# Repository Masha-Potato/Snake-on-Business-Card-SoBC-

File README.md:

sobc.kicad_pcb, sobc.kicad_pro, and sobc.kicad_sch are the relevant files to view and edit PCB, the rest are manufacturing files for JLCPCB.

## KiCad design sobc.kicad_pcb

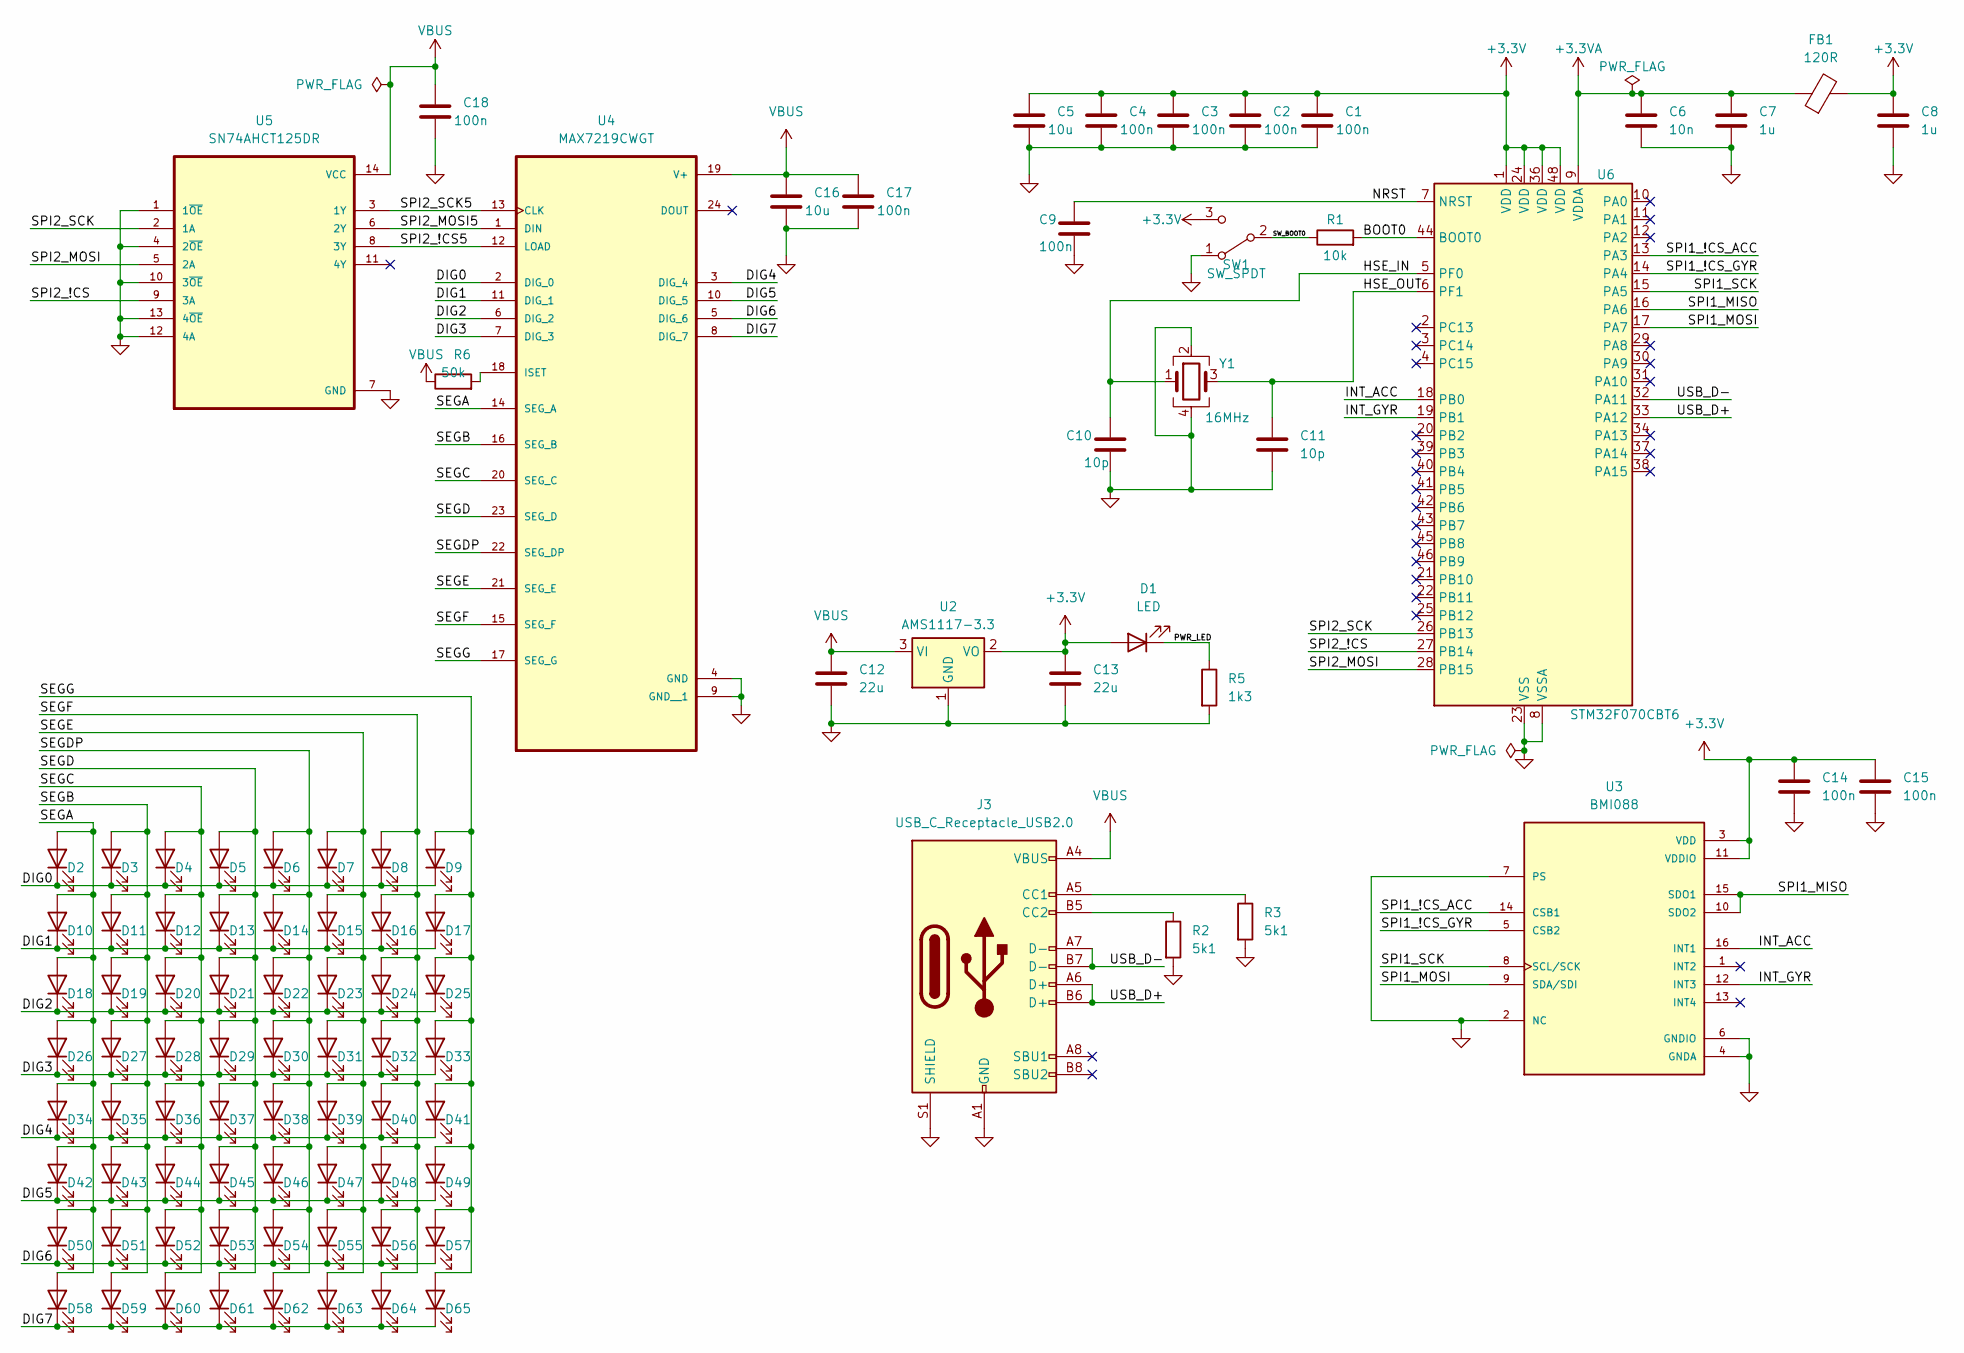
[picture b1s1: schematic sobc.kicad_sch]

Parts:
C1, C2, C3, C4, C9, C14, C15, C17, C18: 100n; C_0402_1005Metric
C5, C16: 10u; C_0603_1608Metric
C6: 10n; C_0402_1005Metric
C7, C8: 1u; C_0402_1005Metric
C10, C11: 10p; C_0402_1005Metric
C12, C13: 22u; C_0805_2012Metric
D1, D2, D3, D4, D5, D6, D7, D8, D9, D10, D11, D12, D13, D14, D15, D16, D17, D18, D19, D20, D21, D22, D23, D24, D25, D26, D27, D28, D29, D30, D31, D32, D33, D34, D35, D36, D37, D38, D39, D40, D41, D42, D43, D44, D45, D46, D47, D48, D49, D50, D51, D52, D53, D54, D55, D56, D57, D58, D59, D60, D61, D62, D63, D64, D65: LED; LED_0603_1608Metric
FB1: 120R; L_0603_1608Metric
J3: USB_C_Receptacle_USB2.0; USB_C_Receptacle_HRO_TYPE-C-31-M-12
R1: 10k; R_0402_1005Metric
R2, R3: 5k1; R_0402_1005Metric
R5: 1k3; R_0402_1005Metric
R6: 50k; R_0402_1005Metric
SW1: SW_SPDT; SW_SPDT_PCM12
U2: AMS1117-3.3; SOT-223-3_TabPin2
U3: BMI088; PQFN50P450X300X100-16N
U4: MAX7219CWGT; SOIC127P1032X265-24N
U5: SN74AHCT125DR; SOIC127P600X175-14N
U6: STM32F070CBT6; LQFP-48_7x7mm_P0.5mm
Y1: 16MHz; Crystal_SMD_3225-4Pin_3.2x2.5mm

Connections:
+3.3V: C1.1, C2.1, C3.1, C4.1, C5.1, C8.1, C13.1, C14.1, C15.1, D1.2 (A), FB1.2, SW1.3 (C), U2.2 (VO), U3.3 (VDD), U3.11 (VDDIO), U6.1 (VDD), U6.24 (VDD), U6.36 (VDD), U6.48 (VDD); also elsewhere on the board
+3.3VA: C6.1, C7.1, FB1.1, U6.9 (VDDA)
/BOOT0: R1.2, U6.44 (BOOT0)
/DIG0: D2.1 (K), D3.1 (K), D4.1 (K), D5.1 (K), D6.1 (K), D7.1 (K), D8.1 (K), D9.1 (K), U4.2 (DIG_0); also elsewhere on the board
/DIG1: D10.1 (K), D11.1 (K), D12.1 (K), D13.1 (K), D14.1 (K), D15.1 (K), D16.1 (K), D17.1 (K), U4.11 (DIG_1); also elsewhere on the board
/DIG2: D18.1 (K), D19.1 (K), D20.1 (K), D21.1 (K), D22.1 (K), D23.1 (K), D24.1 (K), D25.1 (K), U4.6 (DIG_2); also elsewhere on the board
/DIG3: D26.1 (K), D27.1 (K), D28.1 (K), D29.1 (K), D30.1 (K), D31.1 (K), D32.1 (K), D33.1 (K), U4.7 (DIG_3); also elsewhere on the board
/DIG4: D34.1 (K), D35.1 (K), D36.1 (K), D37.1 (K), D38.1 (K), D39.1 (K), D40.1 (K), D41.1 (K), U4.3 (DIG_4); also elsewhere on the board
/DIG5: D42.1 (K), D43.1 (K), D44.1 (K), D45.1 (K), D46.1 (K), D47.1 (K), D48.1 (K), D49.1 (K), U4.10 (DIG_5); also elsewhere on the board
/DIG6: D50.1 (K), D51.1 (K), D52.1 (K), D53.1 (K), D54.1 (K), D55.1 (K), D56.1 (K), D57.1 (K), U4.5 (DIG_6); also elsewhere on the board
/DIG7: D58.1 (K), D59.1 (K), D60.1 (K), D61.1 (K), D62.1 (K), D63.1 (K), D64.1 (K), D65.1 (K), U4.8 (DIG_7); also elsewhere on the board
/HSE_IN: C10.1, U6.5 (PF0), Y1.1
/HSE_OUT: C11.1, U6.6 (PF1), Y1.3
/INT_ACC: U3.16 (INT1), U6.18 (PB0)
/INT_GYR: U3.12 (INT3), U6.19 (PB1)
/NRST: C9.1, U6.7 (NRST)
/PWR_LED: D1.1 (K), R5.1
/SEGA: D2.2 (A), D10.2 (A), D18.2 (A), D26.2 (A), D34.2 (A), D42.2 (A), D50.2 (A), D58.2 (A), U4.14 (SEG_A); also elsewhere on the board
/SEGB: D3.2 (A), D11.2 (A), D19.2 (A), D27.2 (A), D35.2 (A), D43.2 (A), D51.2 (A), D59.2 (A), U4.16 (SEG_B); also elsewhere on the board
/SEGC: D4.2 (A), D12.2 (A), D20.2 (A), D28.2 (A), D36.2 (A), D44.2 (A), D52.2 (A), D60.2 (A), U4.20 (SEG_C); also elsewhere on the board
/SEGD: D5.2 (A), D13.2 (A), D21.2 (A), D29.2 (A), D37.2 (A), D45.2 (A), D53.2 (A), D61.2 (A), U4.23 (SEG_D); also elsewhere on the board
/SEGDP: D6.2 (A), D14.2 (A), D22.2 (A), D30.2 (A), D38.2 (A), D46.2 (A), D54.2 (A), D62.2 (A), U4.22 (SEG_DP); also elsewhere on the board
/SEGE: D7.2 (A), D15.2 (A), D23.2 (A), D31.2 (A), D39.2 (A), D47.2 (A), D55.2 (A), D63.2 (A), U4.21 (SEG_E); also elsewhere on the board
/SEGF: D8.2 (A), D16.2 (A), D24.2 (A), D32.2 (A), D40.2 (A), D48.2 (A), D56.2 (A), D64.2 (A), U4.15 (SEG_F); also elsewhere on the board
/SEGG: D9.2 (A), D17.2 (A), D25.2 (A), D33.2 (A), D41.2 (A), D49.2 (A), D57.2 (A), D65.2 (A), U4.17 (SEG_G); also elsewhere on the board
/SPI1_!CS_ACC: U3.14 (CSB1), U6.13 (PA3)
/SPI1_!CS_GYR: U3.5 (CSB2), U6.14 (PA4)
/SPI1_MISO: U3.10 (SDO2), U3.15 (SDO1), U6.16 (PA6)
/SPI1_MOSI: U3.9 (SDA/SDI), U6.17 (PA7)
/SPI1_SCK: U3.8 (SCL/SCK), U6.15 (PA5)
/SPI2_!CS: U5.9 (3A), U6.27 (PB14); also elsewhere on the board
/SPI2_MOSI: U5.5 (2A), U6.28 (PB15); also elsewhere on the board
/SPI2_SCK: U5.2 (1A), U6.26 (PB13); also elsewhere on the board
/SW_BOOT0: R1.1, SW1.2 (B)
/USB_D+: J3.A6 (D+), J3.B6 (D+), U6.33 (PA12)
/USB_D-: J3.A7 (D-), J3.B7 (D-), U6.32 (PA11)
GND: C1.2, C2.2, C3.2, C4.2, C5.2, C6.2, C7.2, C8.2, C9.2, C10.2, C11.2, C12.2, C13.2, C14.2, C15.2, C16.2, C17.2, C18.2, J3.A1 (GND), J3.A12 (GND), J3.B1 (GND), J3.B12 (GND), J3.S1 (SHIELD), R2.2, R3.2, R5.2, SW1.1 (A), U2.1 (GND), U3.2 (NC), U3.4 (GNDA), U3.6 (GNDIO), U3.7 (PS), U4.4 (GND), U4.9 (GND__1), U5.1 (1~OE), U5.4 (2~OE), U5.7 (GND), U5.10 (3~OE), U5.12 (4A), U5.13 (4~OE), U6.8 (VSSA), U6.23 (VSS), U6.35 (VSS), U6.47 (VSS), Y1.2, Y1.4; also elsewhere on the board
unnamed: J3.A5 (CC1), R3.1
unnamed: J3.B5 (CC2), R2.1
unnamed 42: R6.2, U4.18 (ISET); also elsewhere on the board
unnamed: U4.1 (DIN), U5.6 (2Y)
unnamed: U4.12 (LOAD), U5.8 (3Y)
unnamed: U4.13 (CLK), U5.3 (1Y)
VBUS: C12.1, C16.1, C17.1, C18.1, J3.A4 (VBUS), J3.A9 (VBUS), J3.B4 (VBUS), J3.B9 (VBUS), R6.1, U2.3 (VI), U4.19 (V+), U5.14 (VCC); also elsewhere on the board

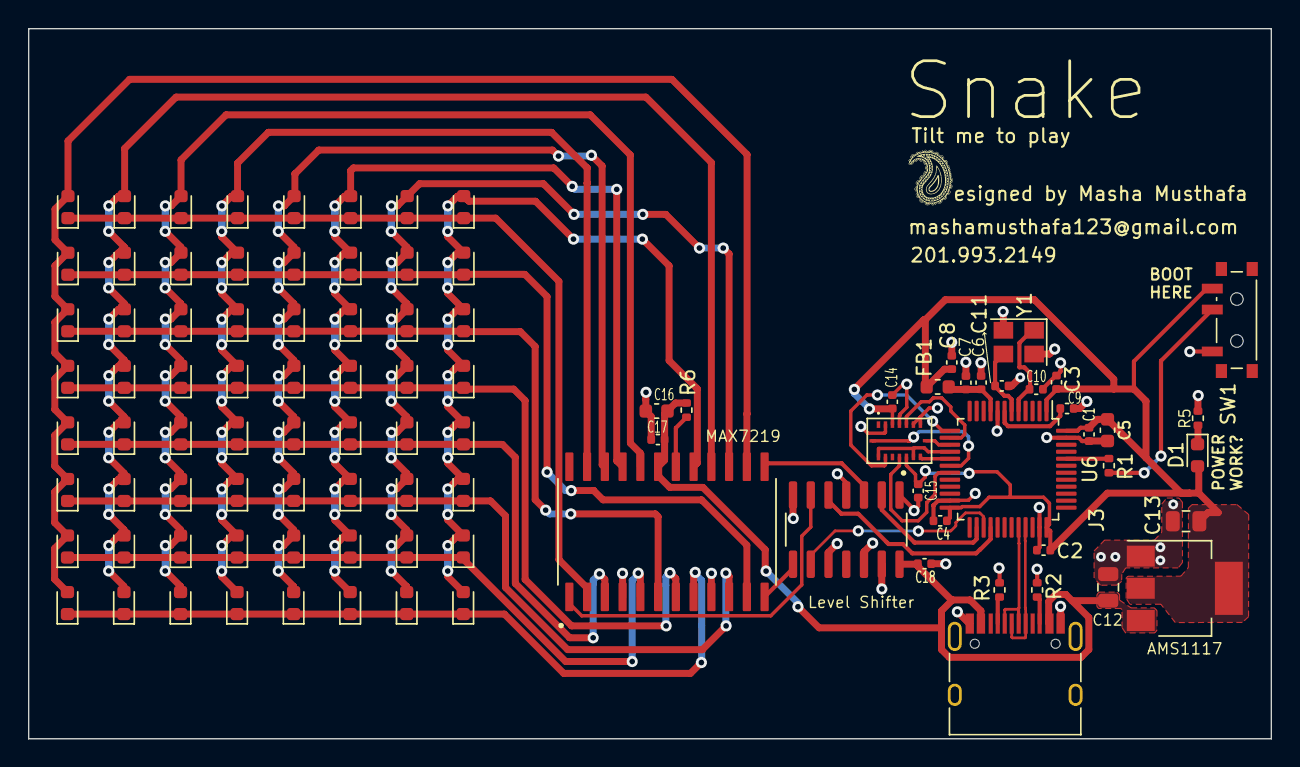
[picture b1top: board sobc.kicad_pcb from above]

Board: 2 copper layers, 88.9 x 50.8 mm, 97 parts (0 on the bottom side), 44 nets.

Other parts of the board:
AMS1117: AMS1117-3.3; SOT-223-3_TabPin2
Level Shifter: SN74AHCT125DR; SOIC127P600X175-14N
MAX7219: MAX7219CWGT; SOIC127P1032X265-24N

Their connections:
+3.3V: AMS1117.2 (VO); also elsewhere on the board
/DIG0: MAX7219.2 (DIG_0); also elsewhere on the board
/DIG1: MAX7219.11 (DIG_1); also elsewhere on the board
/DIG2: MAX7219.6 (DIG_2); also elsewhere on the board
/DIG3: MAX7219.7 (DIG_3); also elsewhere on the board
/DIG4: MAX7219.3 (DIG_4); also elsewhere on the board
/DIG5: MAX7219.10 (DIG_5); also elsewhere on the board
/DIG6: MAX7219.5 (DIG_6); also elsewhere on the board
/DIG7: MAX7219.8 (DIG_7); also elsewhere on the board
/SEGA: MAX7219.14 (SEG_A); also elsewhere on the board
/SEGB: MAX7219.16 (SEG_B); also elsewhere on the board
/SEGC: MAX7219.20 (SEG_C); also elsewhere on the board
/SEGD: MAX7219.23 (SEG_D); also elsewhere on the board
/SEGDP: MAX7219.22 (SEG_DP); also elsewhere on the board
/SEGE: MAX7219.21 (SEG_E); also elsewhere on the board
/SEGF: MAX7219.15 (SEG_F); also elsewhere on the board
/SEGG: MAX7219.17 (SEG_G); also elsewhere on the board
/SPI2_!CS: Level Shifter.9 (3A); also elsewhere on the board
/SPI2_!CS5: Level Shifter.8 (3Y), MAX7219.12 (LOAD)
/SPI2_MOSI: Level Shifter.5 (2A); also elsewhere on the board
/SPI2_MOSI5: Level Shifter.6 (2Y), MAX7219.1 (DIN)
/SPI2_SCK: Level Shifter.2 (1A); also elsewhere on the board
/SPI2_SCK5: Level Shifter.3 (1Y), MAX7219.13 (CLK)
GND: AMS1117.1 (GND), Level Shifter.1 (1~OE), Level Shifter.4 (2~OE), Level Shifter.7 (GND), Level Shifter.10 (3~OE), Level Shifter.12 (4A), Level Shifter.13 (4~OE), MAX7219.4 (GND), MAX7219.9 (GND__1); also elsewhere on the board
unnamed 42: MAX7219.18 (ISET); also elsewhere on the board
VBUS: AMS1117.3 (VI), Level Shifter.14 (VCC), MAX7219.19 (V+); also elsewhere on the board

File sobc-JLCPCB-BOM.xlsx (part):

JLCPCB BOM Tool - BOM Matching
BOM name：sobc-JLCPCB Assembly Order.xlsx |  |  |  | Download Time：2026-01-29 13:04:07 |  |  |  | * Our matching results are updated in real-time, but stock and prices may chang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
PCB Assembled Qty：2 |  |  |  | Est. Total Price：27.6046 (Pre-order parts require a quotation for final pricing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
Your BOM |  |  |  | Matched Parts |  |  |  |  |  |  | Order Information
Designator | Comment | Footprint | JLCPCB Part # | Matches | Part # | Manufacturer | Footprint | Description | Category | Warning | JLCPCB Part # | Product link | Source | Lib Type | MOQ | Availability | My Parts(JLCPCB Parts) | My Parts(Global sourcing & consigned parts) | Rec. Order Qty | Unit Price ($) | Total Price ($)
C7,C8 | 1u | Capacitor_SMD:C_0402_1005Metric |  | Select by Customer | CL05A105KA5NQNC | Samsung Electro-Mechanics | Capacitor_SMD:C_0402_1005Metric | 1uF 25V X5R ±10% 0402 Multilayer Ceramic Capacitors MLCC - SMD/SMT ROHS | Multilayer Ceramic Capacitors MLCC - SMD/SMT |  | C52923 | https://jlcpcb.com/partdetail/53938-CL05A105KA5NQNC/C52923 | In-stock | Basic | 1.0 | 5515255.0 | 0.0 | 0.0 | 20.0 | 0.0033 | 0.066
C1,C2,C3,C4,C9,C14,C15,C17,C18 | 100n | Capacitor_SMD:C_0402_1005Metric |  | Select by Customer | CL05B104KO5NNNC | Samsung Electro-Mechanics | Capacitor_SMD:C_0402_1005Metric | 100nF 16V X7R ±10% 0402 Multilayer Ceramic Capacitors MLCC - SMD/SMT ROHS | Multilayer Ceramic Capacitors MLCC - SMD/SMT |  | C1525 | https://jlcpcb.com/partdetail/1877-CL05B104KO5NNNC/C1525 | In-stock | Basic | 1.0 | 4.1567469E7 | 0.0 | 0.0 | 28.0 | 0.0013 | 0.0364
U4 | MAX7219CWGT | MAX7219CWG_T:SOIC127P1032X265-24N |  | Select by Customer | MAX7219CWG+T | Analog Devices Inc./Maxim Integrated | MAX7219CWG_T:SOIC127P1032X265-24N | 0℃~+70℃ 4-Wire Serial Interface 4V~5.5V 760mW Adjustable Glow、Common Cathode SO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 | Digital Tube Drivers |  | C9964 | https://jlcpcb.com/partdetail/10499-MAX7219CWGT/C9964 | In-stock | Extended | 1.0 | 2065.0 | 0.0 | 0.0 | 2.0 | 2.6353 | 5.2706
Y1 | 16MHz | Crystal:Crystal_SMD_3225-4Pin_3.2x2.5mm |  | Select by Customer | X322516MMB4SI | YXC Crystal Oscillators | Crystal:Crystal_SMD_3225-4Pin_3.2x2.5mm | -40℃~+85℃ 10pF 16MHz Crystal Oscillator ±10ppm ±20ppm SMD3225-4P Crystals ROHS | Crystals |  | C112972 | https://jlcpcb.com/partdetail/114206-X322516MMB4SI/C112972 | In-stock | Extended | 1.0 | 9183.0 | 0.0 | 0.0 | 6.0 | 0.0836 | 0.5016
D1,D2,D3,D4,D5,D6,D7,D8,D9,D10,D11,D12,D13,D14,D15,D16,D17,D18,D19,D20,D21,D22,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 | LED | LED_SMD:LED_0603_1608Metric |  | Select by Customer | KT-0603W | Hubei KENTO Elec | LED_SMD:LED_0603_1608Metric | 100mW 120° 2.6V~3.1V 360mcd 5mA Discrete Diode Top-mount White Yellow Lens 0603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 | LED Indication - Discrete |  | C2290 | https://jlcpcb.com/partdetail/Hubei_KENTOElec-KT0603W/C2290 | In-stock | Basic | 1.0 | 2016285.0 | 0.0 | 0.0 | 140.0 | 0.0107 | 1.498
R1,R7 | 10k | Resistor_SMD:R_0402_1005Metric |  | Select by Customer | RCA0210KFLF | HKR(Hong Kong Resistors) | Resistor_SMD:R_0402_1005Metric | -55℃~+155℃ 10kΩ 50V 62.5mW Thick Film Resistor ±1% ±200ppm/℃ 0402 Chip Resistor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 | Chip Resistor - Surface Mount |  | C22369472 | https://jlcpcb.com/partdetail/23848502-RCA0210KFLF/C22369472 | In-stock | Extended | 1.0 | 39888.0 | 0.0 | 0.0 | 20.0 | 6.0E-4 | 0.012
C6 | 10n | Capacitor_SMD:C_0402_1005Metric |  | Select by Customer | CL05B103KB5NNNC | Samsung Electro-Mechanics | Capacitor_SMD:C_0402_1005Metric | 10nF 50V X7R ±10% 0402 Multilayer Ceramic Capacitors MLCC - SMD/SMT ROHS | Multilayer Ceramic Capacitors MLCC - SMD/SMT |  | C15195 | https://jlcpcb.com/partdetail/15869-CL05B103KB5NNNC/C15195 | In-stock | Basic | 1.0 | 3423691.0 | 0.0 | 0.0 | 20.0 | 0.0014 | 0.028
U6 | STM32F070CBT6 | Package_QFP:LQFP-48_7x7mm_P0.5mm |  | Select by System | STM32F070CBT6 | STMicroelectronics | Package_QFP:LQFP-48_7x7mm_P0.5mm | -40℃~+85℃ 128KB 12bit 16KB 2.4V~3.6V 32 Bit 37 48MHz ARM Cortex-M0 Built-in FLA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 | Microcontrollers (MCU/MPU/SOC) |  | C74909 | https://jlcpcb.com/partdetail/STMicroelectronics-STM32F070CB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 | In-stock | Extended | 1.0 | 1266.0 | 0.0 | 0.0 | 2.0 | 1.758 | 3.516
C5,C16 | 10u | Capacitor_SMD:C_0603_1608Metric |  | Select by Customer | CL10A106KP8NNNC | Samsung Electro-Mechanics | Capacitor_SMD:C_0603_1608Metric | 10V 10uF X5R ±10% 0603 Multilayer Ceramic Capacitors MLCC - SMD/SMT ROHS | Multilayer Ceramic Capacitors MLCC - SMD/SMT |  | C19702 | https://jlcpcb.com/partdetail/20411-CL10A106KP8NNNC/C19702 | In-stock | Basic | 1.0 | 1.2636609E7 | 0.0 | 0.0 | 20.0 | 0.0065 | 0.13
U2 | AMS1117-3.3 | Package_TO_SOT_SMD:SOT-223-3_TabPin2 |  | Select by System | AMS1117-3.3 | Advanced Monolithic Systems | Package_TO_SOT_SMD:SOT-223-3_TabPin2 | -40℃~+125℃ 0.003%Vout 1 1.1V@(800mA) 16V 1A 3.3V 5mA 72dB@(120Hz) Fixed Over Cu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 | Voltage Regulators - Linear, Low Drop Out (LDO) Regulators |  | C6186 | https://jlcpcb.com/partdetail/Advanced_MonolithicSystems-AMS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 | In-stock | Basic | 1.0 | 579666.0 | 0.0 | 0.0 | 2.0 | 0.1856 | 0.3712
C12,C13 | 22u | Capacitor_SMD:C_0805_2012Metric |  | Select by Customer | CL21A226MAQNNNE | Samsung Electro-Mechanics | Capacitor_SMD:C_0805_2012Metric | 22uF 25V X5R ±20% 0805 Multilayer Ceramic Capacitors MLCC - SMD/SMT ROHS | Multilayer Ceramic Capacitors MLCC - SMD/SMT |  | C45783 | https://jlcpcb.com/partdetail/46786-CL21A226MAQNNNE/C45783 | In-stock | Basic | 1.0 | 4311672.0 | 0.0 | 0.0 | 20.0 | 0.0263 | 0.526
U5 | SN74AHCT125DR | SN74AHCT125DR (1):SOIC127P600X175-14N |  | Select by System | SN74AHCT125DR | Texas Instruments | SN74AHCT125DR (1):SOIC127P600X175-14N | -40℃~+85℃ 1 20uA 4 4.5V~5.5V 7.5ns@5V,50pF 74AHCT 8mA 8mA Tri-State SOIC-14 Buf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 | Buffers, Drivers, Receivers, Transceivers |  | C155176 | https://jlcpcb.com/partdetail/TexasInstruments-SN74AHCT125DR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 | In-stock | Extended | 1.0 | 4219.0 | 0.0 | 0.0 | 2.0 | 0.3328 | 0.6656
U3 | BMI055 | BMI0882d:PQFN50P450X300X100-16N |  | Select by System | BMI055 | Bosch Sensortec | BMI0882d:PQFN50P450X300X100-16N | -40℃~+85℃ 12bit、16bit 2.4V~3.6V 62uA IMU SPI、I2C X,Y,Z X,Y,Z ±16g ±2000dps LGA-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 | Accelerometers |  | C189620 | https://jlcpcb.com/partdetail/BoschSensortec-BMI055/C189620 | In-stock | Extended | 1.0 | 4998.0 | 0.0 | 0.0 | 2.0 | 6.0287 | 12.0574
J3 | USB_C_Receptacle_USB2.0 | Connector_USB:USB_C_Receptacle_HRO_TYPE-C-31-M-12 |  | Select by System | TYPE-C-31-M-12 | Korean Hroparts Elec | Connector_USB:USB_C_Receptacle_HRO_TYPE-C-31-M-12 | -30℃~+80℃ 1 10,000 cycles 16P 20V 5A 7.35mm Female Surface Mount, Right Angle T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 | USB Connectors |  | C165948 | https://jlcpcb.com/partdetail/Korean_HropartsElec-TYPE_C_31_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 | In-stock | Extended | 1.0 | 372863.0 | 0.0 | 0.0 | 2.0 | 0.1774 | 0.3548
C10,C11 | 10p | Capacitor_SMD:C_0402_1005Metric |  | Select by Customer | CL05C100JB5NNNC | Samsung Electro-Mechanics | Capacitor_SMD:C_0402_1005Metric | 10pF 50V C0G ±5% 0402 Multilayer Ceramic Capacitors MLCC - SMD/SMT ROHS | Multilayer Ceramic Capacitors MLCC - SMD/SMT |  | C32949 | https://jlcpcb.com/partdetail/33914-CL05C100JB5NNNC/C32949 | In-stock | Basic | 1.0 | 1066707.0 | 0.0 | 0.0 | 20.0 | 0.0044 | 0.088
R2,R3 | 5k1 | Resistor_SMD:R_0402_1005Metric |  | Select by System | 0402WGF5101TCE | UNI-ROYAL(Uniroyal Elec) | Resistor_SMD:R_0402_1005Metric | -55℃~+155℃ 5.1kΩ 50V 62.5mW Thick Film Resistor ±1% ±100ppm/℃ 0402 Chip Resisto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 | Chip Resistor - Surface Mount |  | C25905 | https://jlcpcb.com/partdetail/26648-0402WGF5101TCE/C25905 | In-stock | Basic | 1.0 | 3288613.0 | 0.0 | 0.0 | 20.0 | 7.0E-4 | 0.014
FB1 | 120R | Inductor_SMD:L_0603_1608Metric |  | Select by System | BLM18PG121SN1D | Murata Electronics | Inductor_SMD:L_0603_1608Metric | -55℃~+125℃ 1 120Ω@100MHz 2A 50mΩ ±25% 0603 Ferrite Beads ROHS | Ferrite Beads |  | C14709 | https://jlcpcb.com/partdetail/MurataElectronics-BLM18PG121SN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 | In-stock | Basic | 1.0 | 3355601.0 | 0.0 | 0.0 | 20.0 | 0.0063 | 0.126
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
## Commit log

2026-02-12 Added manufacturing files for PCB (gerbers, drill, BOM, and pick and place)
2026-02-12 Uploaded KiCAD schematic and PCB layout files
